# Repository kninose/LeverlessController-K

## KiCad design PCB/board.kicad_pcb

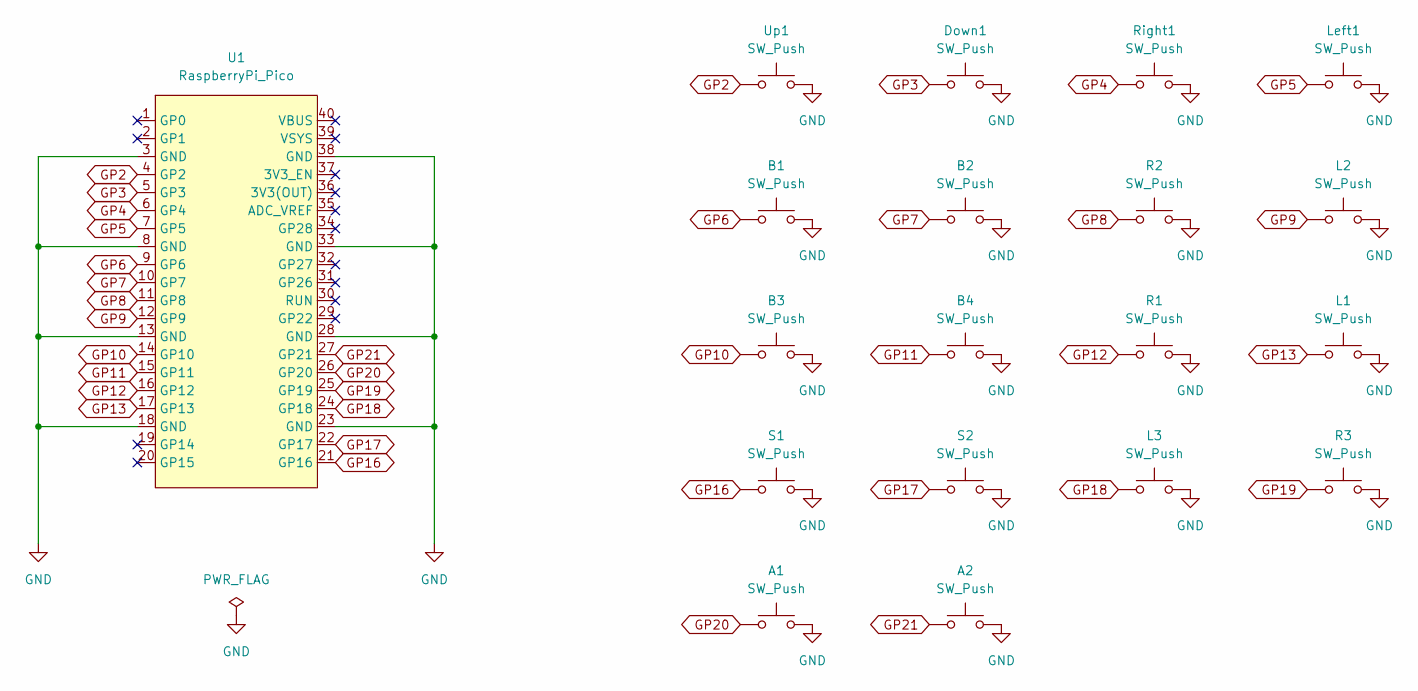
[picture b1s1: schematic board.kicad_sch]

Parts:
A1, A2: SW_Push; Cherry_MX_HotSwap_1U
B1, B2, B3, B4: SW_Push; Cherry_MX_HotSwap_1U
Down1: SW_Push; Cherry_MX_HotSwap_1U
L1, L2: SW_Push; Cherry_MX_HotSwap_1U
L3: SW_Push; Cherry_MX_HotSwap_2U
Left1: SW_Push; Cherry_MX_HotSwap_1U
R1, R2: SW_Push; Cherry_MX_HotSwap_1U
R3: SW_Push; Cherry_MX_HotSwap_2U
Right1: SW_Push; Cherry_MX_HotSwap_1U
S1: SW_Push; Cherry_MX_HotSwap_2.25U
S2: SW_Push; Cherry_MX_HotSwap_2.75U
U1: RaspberryPi_Pico
Up1: SW_Push; Cherry_MX_HotSwap_1U

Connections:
GND: A1.2, A2.2, B1.2, B2.2, B3.2, B4.2, Down1.2, L1.2, L2.2, L3.2, Left1.2, R1.2, R2.2, R3.2, Right1.2, S1.2, S2.2, U1.3 (GND), U1.8 (GND), U1.13 (GND), U1.18 (GND), U1.23 (GND), U1.28 (GND), U1.33 (GND), U1.38 (GND), Up1.2
GP2: U1.4 (GP2), Up1.1
GP3: Down1.1, U1.5 (GP3)
GP4: Right1.1, U1.6 (GP4)
GP5: Left1.1, U1.7 (GP5)
GP6: B1.1, U1.9 (GP6)
GP7: B2.1, U1.10 (GP7)
GP8: R2.1, U1.11 (GP8)
GP9: L2.1, U1.12 (GP9)
GP10: B3.1, U1.14 (GP10)
GP11: B4.1, U1.15 (GP11)
GP12: R1.1, U1.16 (GP12)
GP13: L1.1, U1.17 (GP13)
GP16: S1.1, U1.21 (GP16)
GP17: S2.1, U1.22 (GP17)
GP18: L3.1, U1.24 (GP18)
GP19: R3.1, U1.25 (GP19)
GP20: A1.1, U1.26 (GP20)
GP21: A2.1, U1.27 (GP21)

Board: 2 copper layers, 19 parts (1 on the bottom side), 19 nets.
